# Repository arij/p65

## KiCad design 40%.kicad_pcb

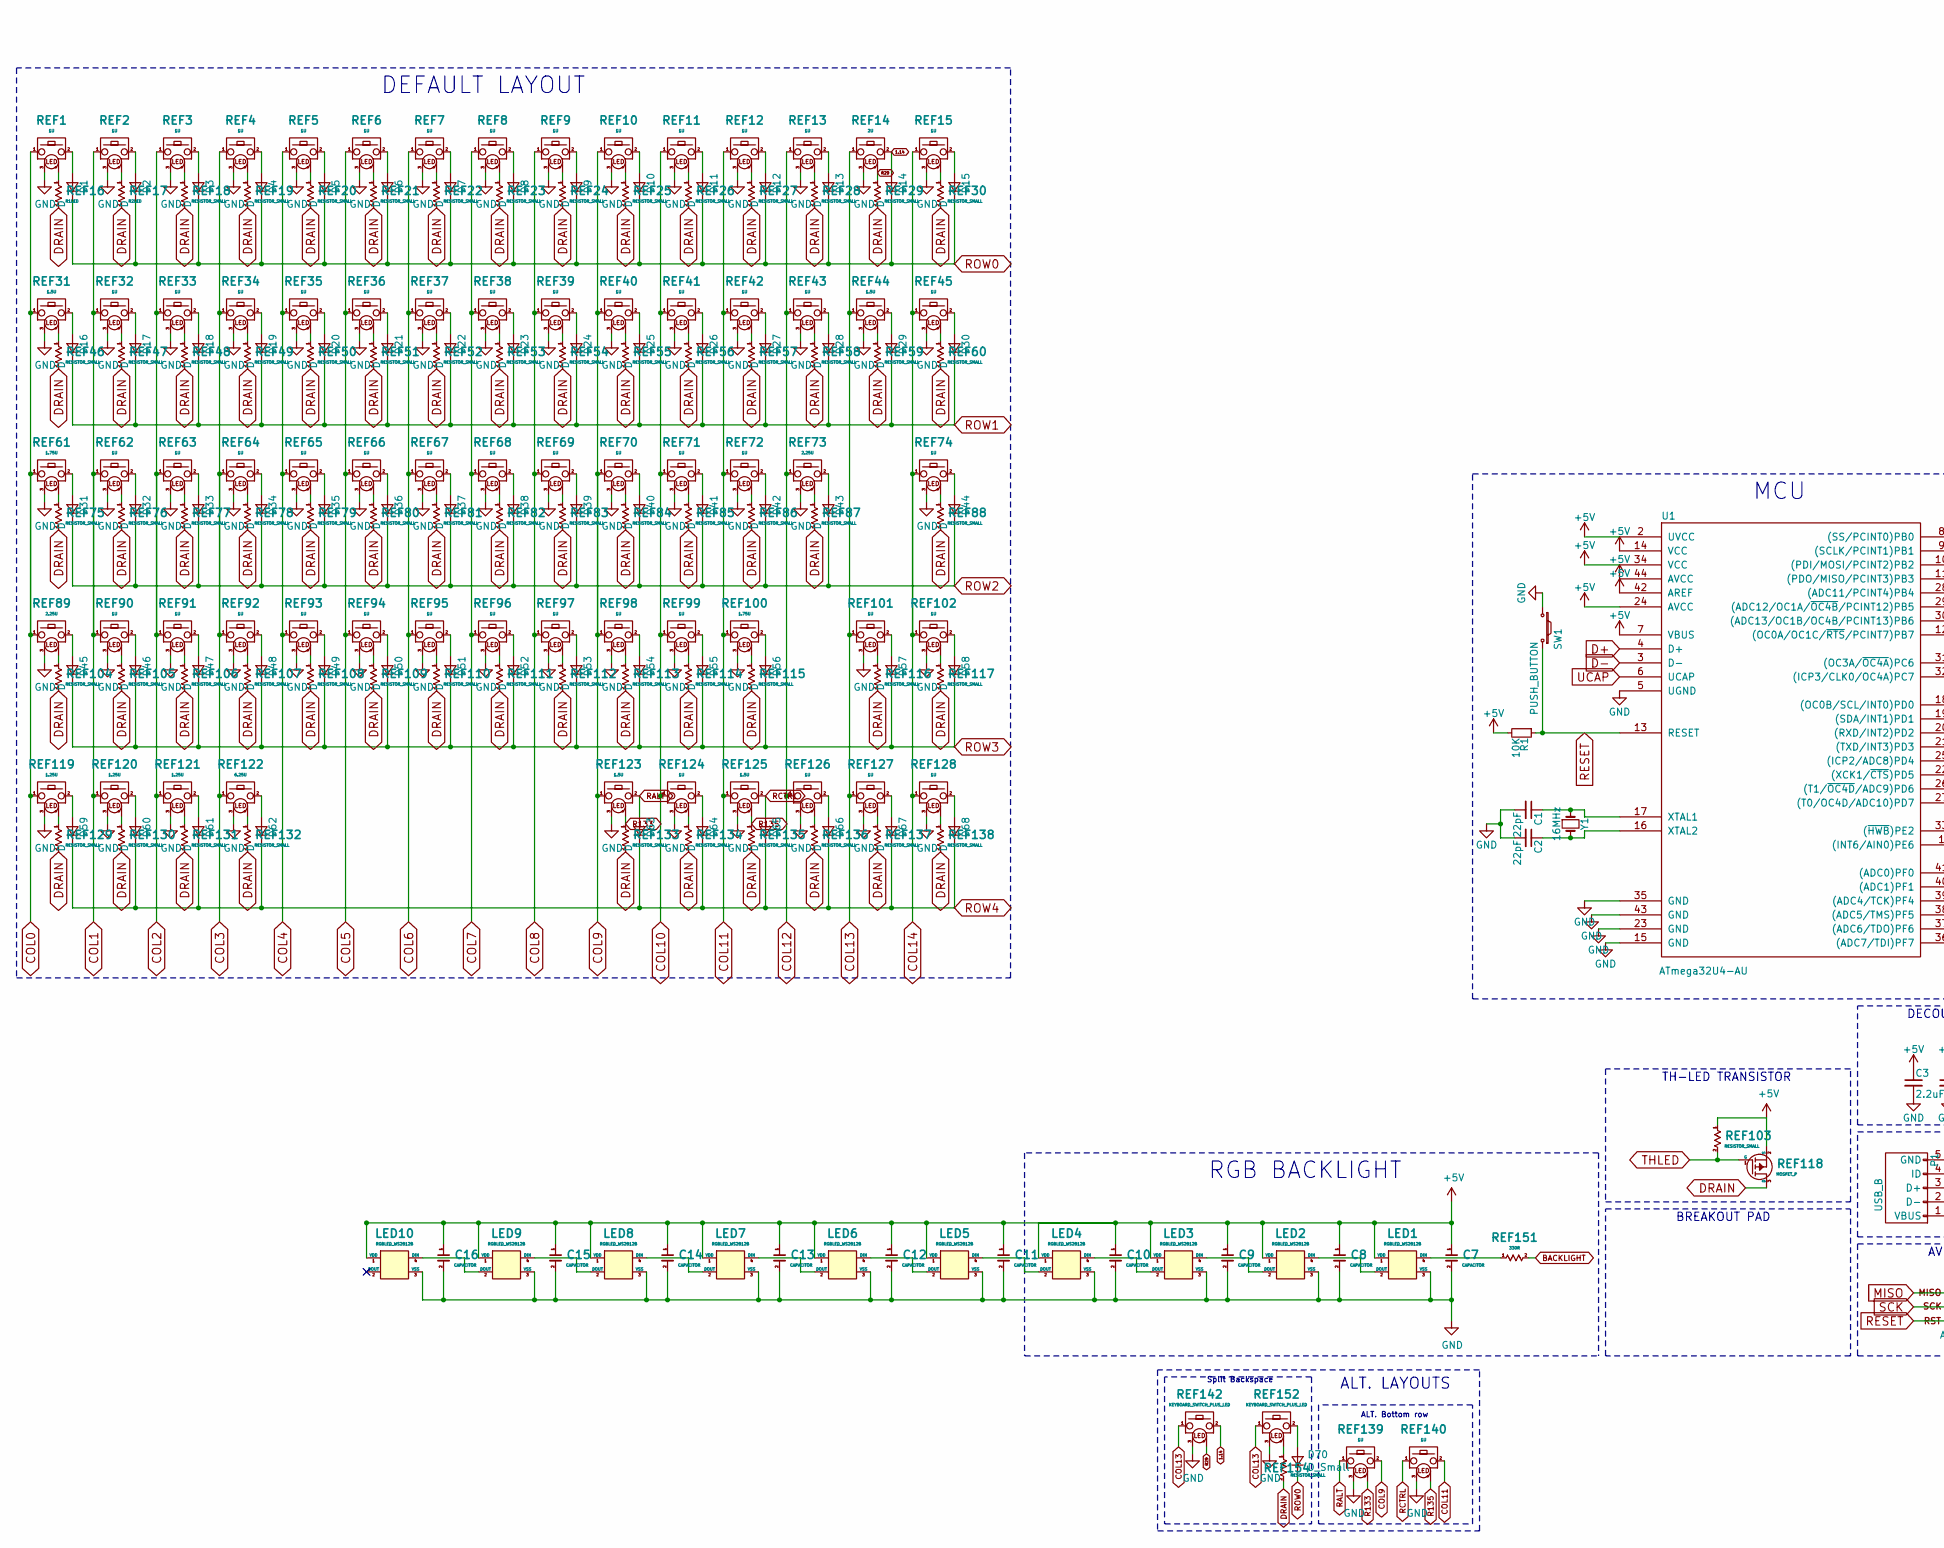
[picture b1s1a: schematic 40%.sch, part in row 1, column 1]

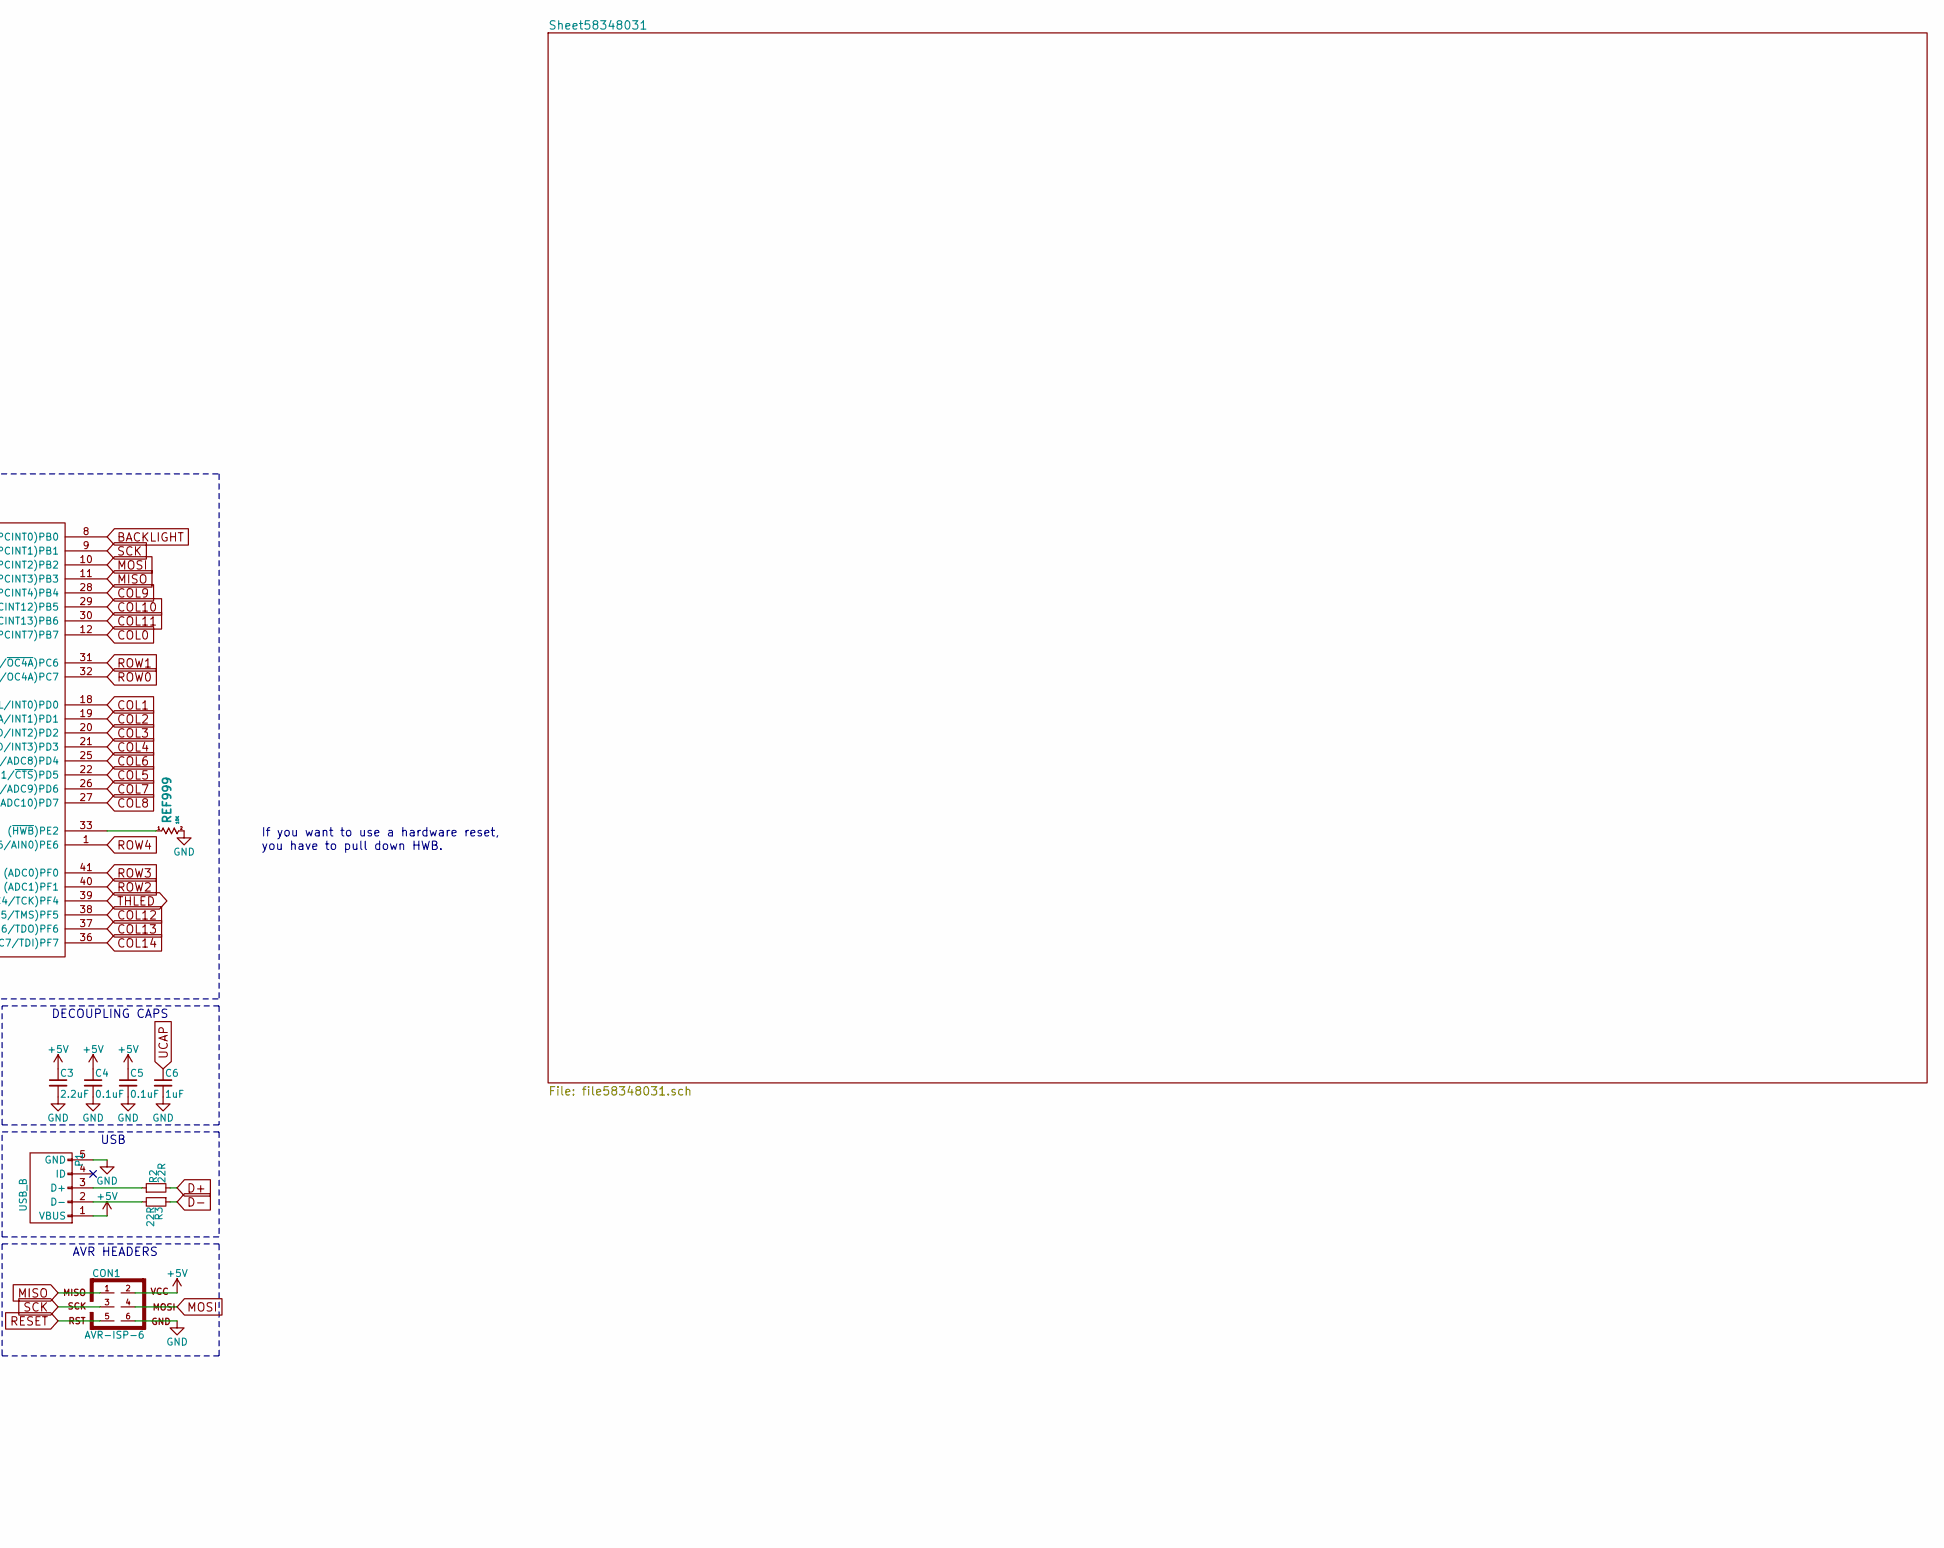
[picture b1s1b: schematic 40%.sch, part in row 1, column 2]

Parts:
C1, C2: 22pF; C_0805
C3: 2.2uF; C_0805
C4, C5: 0.1uF; C_0805
C6: 1uF; C_0805
C7, C8, C9, C10, C11, C12, C13, C14, C15, C16: CAPACITOR; 0805_CAPACITOR
CON1: AVR-ISP-6
D1, D2, D3, D4, D5, D6, D7, D8, D9, D10, D11, D12, D13, D14, D15, D16, D17, D18, D19, D20, D21, D22, D23, D24, D25, D26, D27, D28, D29, D30, D31, D32, D33, D34, D35, D36, D37, D38, D39, D40, D41, D42, D43, D44, D45, D46, D47, D48, D49, D50, D51, D52, D53, D54, D55, D56, D57, D58, D59, D60, D61, D62, D63, D64, D65, D66, D67, D68: D; SOD-323
D70: D_Small; SOD-323
LED1, LED2, LED3, LED4, LED5, LED6, LED7, LED8, LED9, LED10: RGBLED_WS2812B
P1: USB_B; 72f6-usb_mini_b_hiroseux60sc-mb-5s8
R1: 10K; R_0603
R2, R3: 22R; R_0603
REF1, REF2, REF3, REF4, REF5, REF6, REF7, REF8, REF9, REF10, REF11, REF12, REF13, REF15, REF32, REF33, REF34, REF35, REF36, REF37, REF38, REF39, REF40, REF41, REF42, REF43, REF45, REF62, REF63, REF64, REF65, REF66, REF67, REF68, REF69, REF70, REF71, REF72, REF74, REF90, REF91, REF92, REF93, REF94, REF95, REF96, REF97, REF98, REF99, REF101, REF102, REF124, REF126, REF127, REF128, REF139, REF140: 1U; 100U_MX&ALPS&IN_SWITCH_LED_WSS
REF14: 2U; 200U_MX&ALPS&IN_SWITCH_LED_WSS
REF16: R1LED; R_0603
REF17: R2LED; R_0603
REF18, REF19, REF20, REF21, REF22, REF23, REF24, REF25, REF26, REF27, REF28, REF29, REF30, REF46, REF47, REF48, REF49, REF50, REF51, REF52, REF53, REF54, REF55, REF56, REF57, REF58, REF59, REF60, REF75, REF76, REF77, REF78, REF79, REF80, REF81, REF82, REF83, REF84, REF85, REF86, REF87, REF88, REF103, REF104, REF105, REF106, REF107, REF108, REF109, REF110, REF111, REF112, REF113, REF114, REF115, REF116, REF117, REF129, REF130, REF131, REF132, REF133, REF134, REF135, REF136, REF137, REF138, REF154: RESISTOR_SMALL; R_0603
REF31, REF44, REF123, REF125: 1.5U; 150U_MX&ALPS&IN_SWITCH_LED_WSS
REF61, REF100: 1.75U; 175U_MX&ALPS&IN_SWITCH_LED_WSS
REF73, REF89: 2.25U; 225U_MX&ALPS&IN_SWITCH_LED_STABS_WSS
REF118: MOSFET_P; SOT23_MOS-P_SI2305
REF119, REF120, REF121: 1.25U; 125U_MX&ALPS&IN_SWITCH_LED_WSS
REF122: 6.25U; 625U_MX&ALPS&IN_SWITCH_LED_STABS_WSS
REF142, REF152: KEYBOARD_SWITCH_PLUS_LED; 100U_MX&ALPS&IN_SWITCH_LED_WSS
REF151: 330R; R_0603
REF999: 10K; R_0603
SW1: PUSH_BUTTON; SW_SPST_B3U-1000P
U1: ATmega32U4-AU; TQFP-44_ATMEGA32U4
Y1: 16MHz; crystal_ABLS7M

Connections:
1.14: D14.2 (A), REF14.2, REF142.2
+5V: C3.1, C4.1, C5.1, C7.1, C8.1, C9.1, C10.1, C11.1, C12.1, C13.1, C14.1, C15.1, C16.1, CON1.2, LED1.1 (VDD), LED2.1 (VDD), LED3.1 (VDD), LED4.1 (VDD), LED5.1 (VDD), LED6.1 (VDD), LED7.1 (VDD), LED8.1 (VDD), LED9.1 (VDD), LED10.1 (VDD), P1.1 (VBUS), R1.2, REF103.1, REF118.2 (S), U1.2 (UVCC), U1.7 (VBUS), U1.14 (VCC), U1.24 (AVCC), U1.34 (VCC), U1.42 (AREF), U1.44 (AVCC)
BACKLIGHT: REF151.2, U1.8 ((SS/PCINT0)PB0)
COL0: REF1.1, REF31.1, REF61.1, REF89.1, REF119.1, U1.12 ((OC0A/OC1C/~RTS~/PCINT7)PB7)
COL1: REF2.1, REF32.1, REF62.1, REF90.1, REF120.1, U1.18 ((OC0B/SCL/INT0)PD0)
COL2: REF3.1, REF33.1, REF63.1, REF91.1, REF121.1, U1.19 ((SDA/INT1)PD1)
COL3: REF4.1, REF34.1, REF64.1, REF92.1, REF122.1, U1.20 ((RXD/INT2)PD2)
COL4: REF5.1, REF35.1, REF65.1, REF93.1, U1.21 ((TXD/INT3)PD3)
COL5: REF6.1, REF36.1, REF66.1, REF94.1, U1.22 ((XCK1/~CTS~)PD5)
COL6: REF7.1, REF37.1, REF67.1, REF95.1, U1.25 ((ICP2/ADC8)PD4)
COL7: REF8.1, REF38.1, REF68.1, REF96.1, U1.26 ((T1/~OC4D~/ADC9)PD6)
COL8: REF9.1, REF39.1, REF69.1, REF97.1, U1.27 ((T0/OC4D/ADC10)PD7)
COL9: REF10.1, REF40.1, REF70.1, REF98.1, REF123.1, REF139.2, U1.28 ((ADC11/PCINT4)PB4)
COL10: REF11.1, REF41.1, REF71.1, REF99.1, REF124.1, U1.29 ((ADC12/OC1A/~OC4B~/PCINT12)PB5)
COL11: REF12.1, REF42.1, REF72.1, REF100.1, REF125.1, REF140.2, U1.30 ((ADC13/OC1B/OC4B/PCINT13)PB6)
COL12: REF13.1, REF43.1, REF73.1, REF126.1, U1.38 ((ADC5/TMS)PF5)
COL13: REF14.1, REF44.1, REF101.1, REF127.1, REF142.1, REF152.1, U1.37 ((ADC6/TDO)PF6)
COL14: REF15.1, REF45.1, REF74.1, REF102.1, REF128.1, U1.36 ((ADC7/TDI)PF7)
D+: R2.2, U1.4 (D+)
D-: R3.1, U1.3 (D-)
DRAIN: REF16.2, REF17.2, REF18.2, REF19.2, REF20.2, REF21.2, REF22.2, REF23.2, REF24.2, REF25.2, REF26.2, REF27.2, REF28.2, REF29.2, REF30.2, REF46.2, REF47.2, REF48.2, REF49.2, REF50.2, REF51.2, REF52.2, REF53.2, REF54.2, REF55.2, REF56.2, REF57.2, REF58.2, REF59.2, REF60.2, REF75.2, REF76.2, REF77.2, REF78.2, REF79.2, REF80.2, REF81.2, REF82.2, REF83.2, REF84.2, REF85.2, REF86.2, REF87.2, REF88.2, REF104.2, REF105.2, REF106.2, REF107.2, REF108.2, REF109.2, REF110.2, REF111.2, REF112.2, REF113.2, REF114.2, REF115.2, REF116.2, REF117.2, REF118.3 (D), REF129.2, REF130.2, REF131.2, REF132.2, REF133.2, REF134.2, REF135.2, REF136.2, REF137.2, REF138.2, REF154.2
GND: C1.2, C2.2, C3.2, C4.2, C5.2, C6.2, C7.2, C8.2, C9.2, C10.2, C11.2, C12.2, C13.2, C14.2, C15.2, C16.2, CON1.6, LED1.3 (VSS), LED2.3 (VSS), LED3.3 (VSS), LED4.3 (VSS), LED5.3 (VSS), LED6.3 (VSS), LED7.3 (VSS), LED8.3 (VSS), LED9.3 (VSS), LED10.3 (VSS), P1.5 (GND), REF1.3, REF2.3, REF3.3, REF4.3, REF5.3, REF6.3, REF7.3, REF8.3, REF9.3, REF10.3, REF11.3, REF12.3, REF13.3, REF14.3, REF15.3, REF31.3, REF32.3, REF33.3, REF34.3, REF35.3, REF36.3, REF37.3, REF38.3, REF39.3, REF40.3, REF41.3, REF42.3, REF43.3, REF44.3, REF45.3, REF61.3, REF62.3, REF63.3, REF64.3, REF65.3, REF66.3, REF67.3, REF68.3, REF69.3, REF70.3, REF71.3, REF72.3, REF73.3, REF74.3, REF89.3, REF90.3, REF91.3, REF92.3, REF93.3, REF94.3, REF95.3, REF96.3, REF97.3, REF98.3, REF99.3, REF100.3, REF101.3, REF102.3, REF119.3, REF120.3, REF121.3, REF122.3, REF123.3, REF124.3, REF125.3, REF126.3, REF127.3, REF128.3, REF139.3, REF140.3, REF142.3, REF152.3, REF999.2, SW1.1, U1.5 (UGND), U1.15 (GND), U1.23 (GND), U1.35 (GND), U1.43 (GND)
MISO: CON1.1, U1.11 ((PDO/MISO/PCINT3)PB3)
MOSI: CON1.4, U1.10 ((PDI/MOSI/PCINT2)PB2)
unnamed: C1.1, U1.17 (XTAL1), Y1.1
unnamed: C2.1, U1.16 (XTAL2), Y1.2
unnamed: D1.2 (A), REF1.2
unnamed: D2.2 (A), REF2.2
unnamed: D3.2 (A), REF3.2
unnamed: D4.2 (A), REF4.2
unnamed: D5.2 (A), REF5.2
unnamed: D6.2 (A), REF6.2
unnamed: D7.2 (A), REF7.2
unnamed: D8.2 (A), REF8.2
unnamed: D9.2 (A), REF9.2
unnamed: D10.2 (A), REF10.2
unnamed: D11.2 (A), REF11.2
unnamed: D12.2 (A), REF12.2
unnamed: D13.2 (A), REF13.2
unnamed: D15.2 (A), REF15.2
unnamed: D16.2 (A), REF31.2
unnamed: D17.2 (A), REF32.2
unnamed: D18.2 (A), REF33.2
unnamed: D19.2 (A), REF34.2
unnamed: D20.2 (A), REF35.2
unnamed: D21.2 (A), REF36.2
unnamed: D22.2 (A), REF37.2
unnamed: D23.2 (A), REF38.2
unnamed: D24.2 (A), REF39.2
unnamed: D25.2 (A), REF40.2
unnamed: D26.2 (A), REF41.2
unnamed: D27.2 (A), REF42.2
unnamed: D28.2 (A), REF43.2
unnamed: D29.2 (A), REF44.2
unnamed: D30.2 (A), REF45.2
unnamed: D31.2 (A), REF61.2
unnamed: D32.2 (A), REF62.2
unnamed: D33.2 (A), REF63.2
unnamed: D34.2 (A), REF64.2
unnamed: D35.2 (A), REF65.2
unnamed: D36.2 (A), REF66.2
unnamed: D37.2 (A), REF67.2
unnamed: D38.2 (A), REF68.2
unnamed: D39.2 (A), REF69.2
unnamed: D40.2 (A), REF70.2
unnamed: D41.2 (A), REF71.2
unnamed: D42.2 (A), REF72.2
unnamed: D43.2 (A), REF73.2
unnamed: D44.2 (A), REF74.2
unnamed: D45.2 (A), REF89.2
unnamed: D46.2 (A), REF90.2
unnamed: D47.2 (A), REF91.2
unnamed: D48.2 (A), REF92.2
unnamed: D49.2 (A), REF93.2
unnamed: D50.2 (A), REF94.2
unnamed: D51.2 (A), REF95.2
unnamed: D52.2 (A), REF96.2
unnamed: D53.2 (A), REF97.2
unnamed: D54.2 (A), REF98.2
unnamed: D55.2 (A), REF99.2
unnamed: D56.2 (A), REF100.2
unnamed: D57.2 (A), REF101.2
unnamed: D58.2 (A), REF102.2
unnamed: D59.2 (A), REF119.2
unnamed: D60.2 (A), REF120.2
unnamed: D61.2 (A), REF121.2
unnamed: D62.2 (A), REF122.2
unnamed: D64.2 (A), REF124.2
unnamed: D66.2 (A), REF126.2
unnamed: D67.2 (A), REF127.2
unnamed: D68.2 (A), REF128.2
unnamed: D70.2 (A), REF152.2
unnamed: LED1.2 (DOUT), LED2.4 (DIN)
unnamed: LED1.4 (DIN), REF151.1
unnamed: LED2.2 (DOUT), LED3.4 (DIN)
unnamed: LED3.2 (DOUT), LED4.4 (DIN)
unnamed: LED4.2 (DOUT), LED5.4 (DIN)
unnamed: LED5.2 (DOUT), LED6.4 (DIN)
unnamed: LED6.2 (DOUT), LED7.4 (DIN)
unnamed: LED7.2 (DOUT), LED8.4 (DIN)
unnamed: LED8.2 (DOUT), LED9.4 (DIN)
unnamed: LED9.2 (DOUT), LED10.4 (DIN)
unnamed: P1.2 (D-), R3.2
unnamed: P1.3 (D+), R2.1
unnamed: REF1.4, REF16.1
unnamed: REF10.4, REF25.1
unnamed: REF11.4, REF26.1
unnamed: REF12.4, REF27.1
unnamed: REF13.4, REF28.1
unnamed: REF15.4, REF30.1
unnamed: REF2.4, REF17.1
unnamed: REF3.4, REF18.1
unnamed: REF4.4, REF19.1
unnamed: REF5.4, REF20.1
unnamed: REF6.4, REF21.1
unnamed: REF7.4, REF22.1
unnamed: REF8.4, REF23.1
unnamed: REF9.4, REF24.1
unnamed: REF31.4, REF46.1
unnamed: REF32.4, REF47.1
unnamed: REF33.4, REF48.1
unnamed: REF34.4, REF49.1
unnamed: REF35.4, REF50.1
unnamed: REF36.4, REF51.1
unnamed: REF37.4, REF52.1
unnamed: REF38.4, REF53.1
unnamed: REF39.4, REF54.1
unnamed: REF40.4, REF55.1
unnamed: REF41.4, REF56.1
unnamed: REF42.4, REF57.1
unnamed: REF43.4, REF58.1
unnamed: REF44.4, REF59.1
unnamed: REF45.4, REF60.1
unnamed: REF61.4, REF75.1
unnamed: REF62.4, REF76.1
unnamed: REF63.4, REF77.1
unnamed: REF64.4, REF78.1
unnamed: REF65.4, REF79.1
unnamed: REF66.4, REF80.1
unnamed: REF67.4, REF81.1
unnamed: REF68.4, REF82.1
unnamed: REF69.4, REF83.1
unnamed: REF70.4, REF84.1
unnamed: REF71.4, REF85.1
unnamed: REF72.4, REF86.1
unnamed: REF73.4, REF87.1
unnamed: REF74.4, REF88.1
unnamed: REF100.4, REF115.1
unnamed: REF101.4, REF116.1
unnamed: REF102.4, REF117.1
unnamed: REF89.4, REF104.1
unnamed: REF90.4, REF105.1
unnamed: REF91.4, REF106.1
unnamed: REF92.4, REF107.1
unnamed: REF93.4, REF108.1
unnamed: REF94.4, REF109.1
unnamed: REF95.4, REF110.1
unnamed: REF96.4, REF111.1
unnamed: REF97.4, REF112.1
unnamed: REF98.4, REF113.1
unnamed: REF99.4, REF114.1
unnamed: REF119.4, REF129.1
unnamed: REF120.4, REF130.1
unnamed: REF121.4, REF131.1
unnamed: REF122.4, REF132.1
unnamed: REF124.4, REF134.1
unnamed: REF126.4, REF136.1
unnamed: REF127.4, REF137.1
unnamed: REF128.4, REF138.1
unnamed: REF152.4, REF154.1
unnamed: REF999.1, U1.33 ((~HWB~)PE2)
R29: REF14.4, REF29.1, REF142.4
R133: REF123.4, REF133.1, REF139.4
R135: REF125.4, REF135.1, REF140.4
RALT: D63.2 (A), REF123.2, REF139.1
RCTRL: D65.2 (A), REF125.2, REF140.1
RESET: CON1.5, R1.1, SW1.2, U1.13 (RESET)
ROW0: D1.1 (K), D2.1 (K), D3.1 (K), D4.1 (K), D5.1 (K), D6.1 (K), D7.1 (K), D8.1 (K), D9.1 (K), D10.1 (K), D11.1 (K), D12.1 (K), D13.1 (K), D14.1 (K), D15.1 (K), D70.1 (K), U1.32 ((ICP3/CLK0/OC4A)PC7)
ROW1: D16.1 (K), D17.1 (K), D18.1 (K), D19.1 (K), D20.1 (K), D21.1 (K), D22.1 (K), D23.1 (K), D24.1 (K), D25.1 (K), D26.1 (K), D27.1 (K), D28.1 (K), D29.1 (K), D30.1 (K), U1.31 ((OC3A/~OC4A~)PC6)
ROW2: D31.1 (K), D32.1 (K), D33.1 (K), D34.1 (K), D35.1 (K), D36.1 (K), D37.1 (K), D38.1 (K), D39.1 (K), D40.1 (K), D41.1 (K), D42.1 (K), D43.1 (K), D44.1 (K), U1.40 ((ADC1)PF1)
ROW3: D45.1 (K), D46.1 (K), D47.1 (K), D48.1 (K), D49.1 (K), D50.1 (K), D51.1 (K), D52.1 (K), D53.1 (K), D54.1 (K), D55.1 (K), D56.1 (K), D57.1 (K), D58.1 (K), U1.41 ((ADC0)PF0)
ROW4: D59.1 (K), D60.1 (K), D61.1 (K), D62.1 (K), D63.1 (K), D64.1 (K), D65.1 (K), D66.1 (K), D67.1 (K), D68.1 (K), U1.1 ((INT6/AIN0)PE6)
SCK: CON1.3, U1.9 ((SCLK/PCINT1)PB1)
THLED: REF103.2, REF118.1 (G), U1.39 ((ADC4/TCK)PF4)
UCAP: C6.1, U1.6 (UCAP)

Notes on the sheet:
AVR HEADERS
USB
DECOUPLING CAPS
BREAKOUT PAD
TH-LED TRANSISTOR
ALT. LAYOUTS
MCU
DEFAULT LAYOUT
RGB BACKLIGHT
Split Backspace
ALT. Bottom row
If you want to use a hardware reset, you have to pull down HWB.

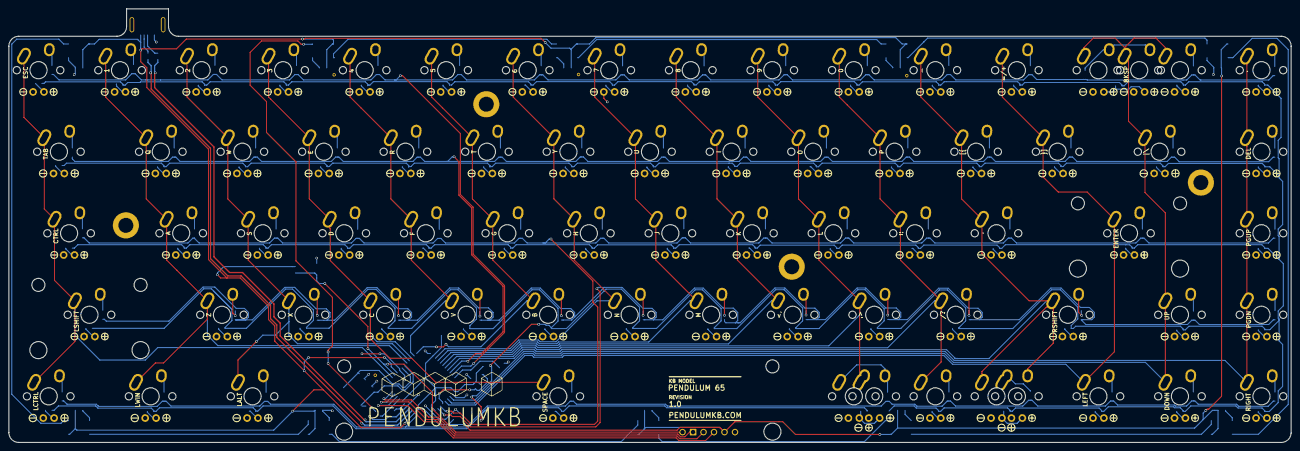
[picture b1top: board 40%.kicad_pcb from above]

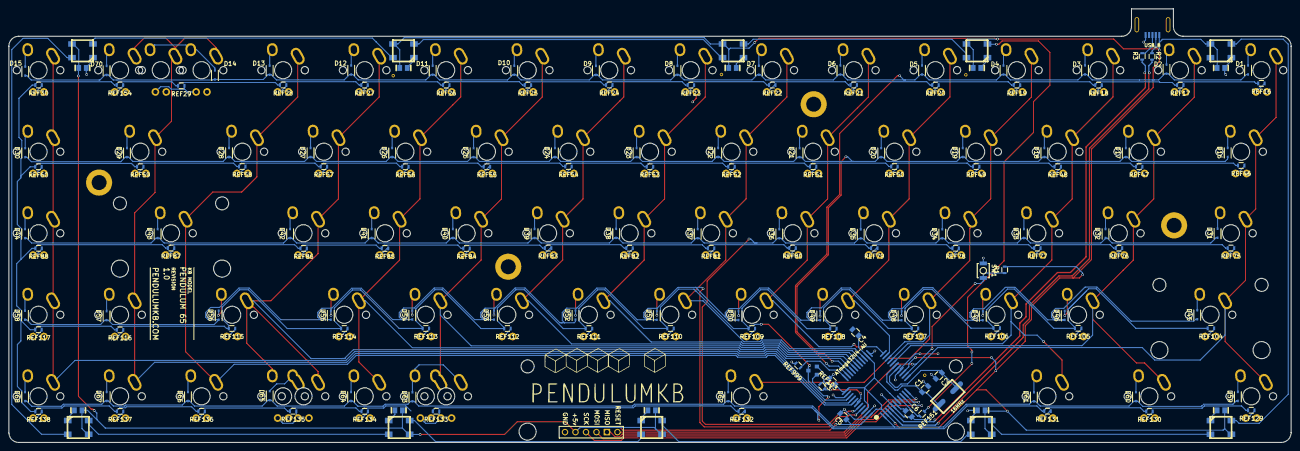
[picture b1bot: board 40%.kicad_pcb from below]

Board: 2 copper layers, 299.6 x 101.3 mm, 258 parts (177 on the bottom side), 185 nets.

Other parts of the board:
OVAL_HOLE: POKER_OVAL_HOLE
OVAL_HOLE#2, OVAL_HOLE#3, OVAL_HOLE#4: POKER_OVAL_HOLE
P65NP, P65NP#2: p65nameplate
VIA: VIA
VIA#2, VIA#3, VIA#4: VIA

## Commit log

2017-03-09 :lollipop: Added .gitattributes & .gitignore files
2017-03-25 License file
